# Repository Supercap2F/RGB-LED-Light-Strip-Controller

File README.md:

# RGB-LED-Light-Strip-Controller
This project is a controller for a 12V RGB LED strip. It uses the PIC12F1840 for control.

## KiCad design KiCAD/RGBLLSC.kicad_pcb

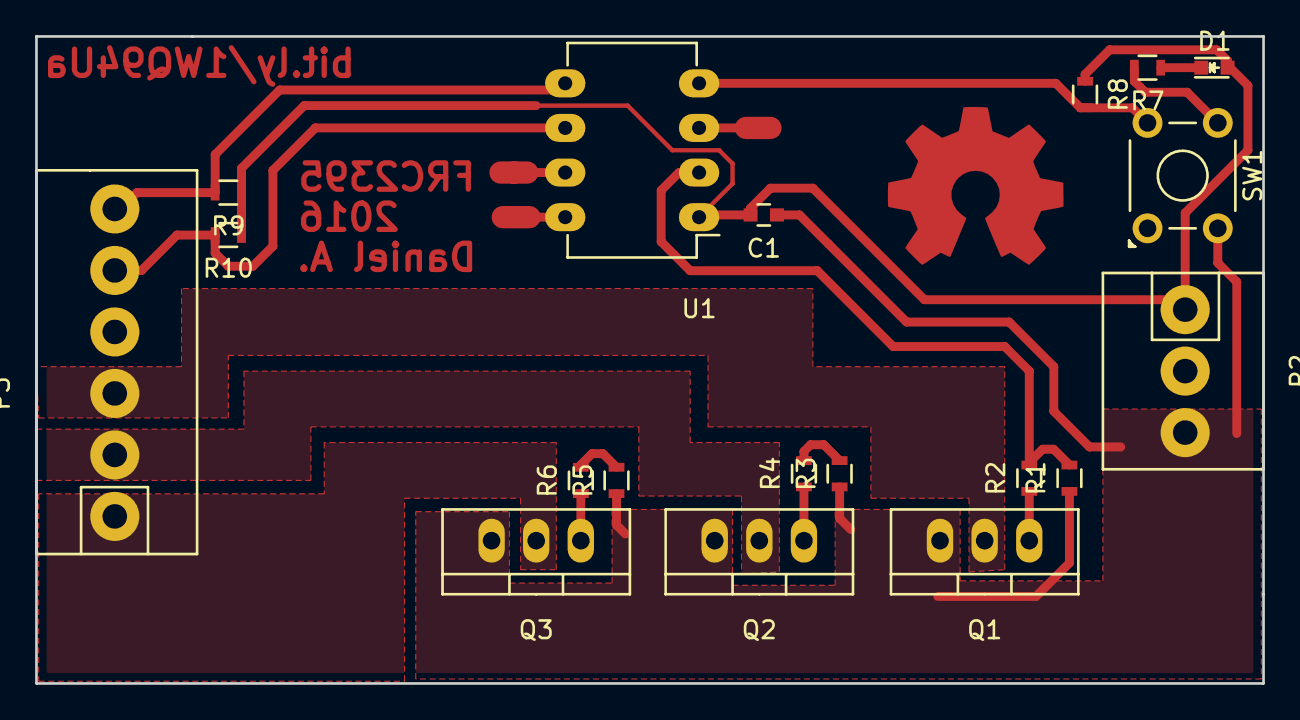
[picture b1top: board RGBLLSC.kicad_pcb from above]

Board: 2 copper layers, 69.9 x 36.8 mm, 19 parts (0 on the bottom side), 16 nets.

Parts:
C1: 100n; C_0603
D1: LED; LED_0603
P2: PWR IN; Screw-Terminal-Thingy-3pin-3.5mm
P3: MAIN OUT; Screw-Terminal-Thingy-6pin-3.5mm
Q1, Q2, Q3: FQP30N06L; TO-220_Neutral123_Vertical
R1, R3, R5: 1M; R_0603
R2, R4, R6: 100; R_0603
R7: R; R_0603
R8: 10K; R_0603
R9, R10: 4.7K; R_0603
SW1: SW_PUSH; SW_TH_Tactile_Omron_B3F-10xx
U1: PIC12F1840; DIP-8_W7.62mm_LongPads

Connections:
+5V: C1.2, D1.2, P2.1, R8.1, R9.1, R10.1, U1.1
+12V: P2.2, P3.4
GND: C1.1, P2.3, Q1.3, Q2.3, Q3.3, R1.1, R3.1, R5.1, R7.2, SW1.3, SW1.4, U1.8
unnamed: D1.1, R7.1
unnamed: R8.2, SW1.1, SW1.2, U1.4
unnamed: R5.2, R6.2, U1.7
unnamed: P3.5, R10.2, U1.6
unnamed: P3.1, Q3.2
unnamed: P3.2, Q2.2
unnamed: P3.3, Q1.2
unnamed: P3.6, R9.2, U1.5
unnamed: Q1.1, R2.1
unnamed: Q2.1, R4.1
unnamed: Q3.1, R6.1
unnamed: R1.2, R2.2, U1.2
unnamed: R3.2, R4.2, U1.3

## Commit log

2016-01-21 Added KiCAD files
2016-01-21 Created A README.md
2016-01-22 Added Code and Updated Schematic
2016-01-22 Updated Code
2016-01-23 Changed Code
2016-01-23 Finished RGB LED Algorithm
2016-01-23 Added Coments to Code
2016-01-23 Added Comments to Code
2016-01-25 Added I2C Code
2016-01-25 Added Interrupt Vector Code
2016-01-26 Worked out almost all bugs - Still needs some tweeks
2016-01-26 Finished Code
2016-01-26 Cleaned Project
2016-01-28 Updated Schematic
2016-01-28 Started PCB Design
2016-01-28 Updated PCB Design and Schematic
2016-01-28 Finished PCB
2016-01-28 Added OSHWA Logo to PCB
2016-01-28 Added Gerber Files
2016-01-28 Updated Gerbers
2016-01-29 Added Project Images
2016-01-29 Finished V1.0
2016-02-03 Fixed Inverted Light color prob
